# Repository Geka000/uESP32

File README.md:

# uESP32

Small development board for ESP-WROOM32

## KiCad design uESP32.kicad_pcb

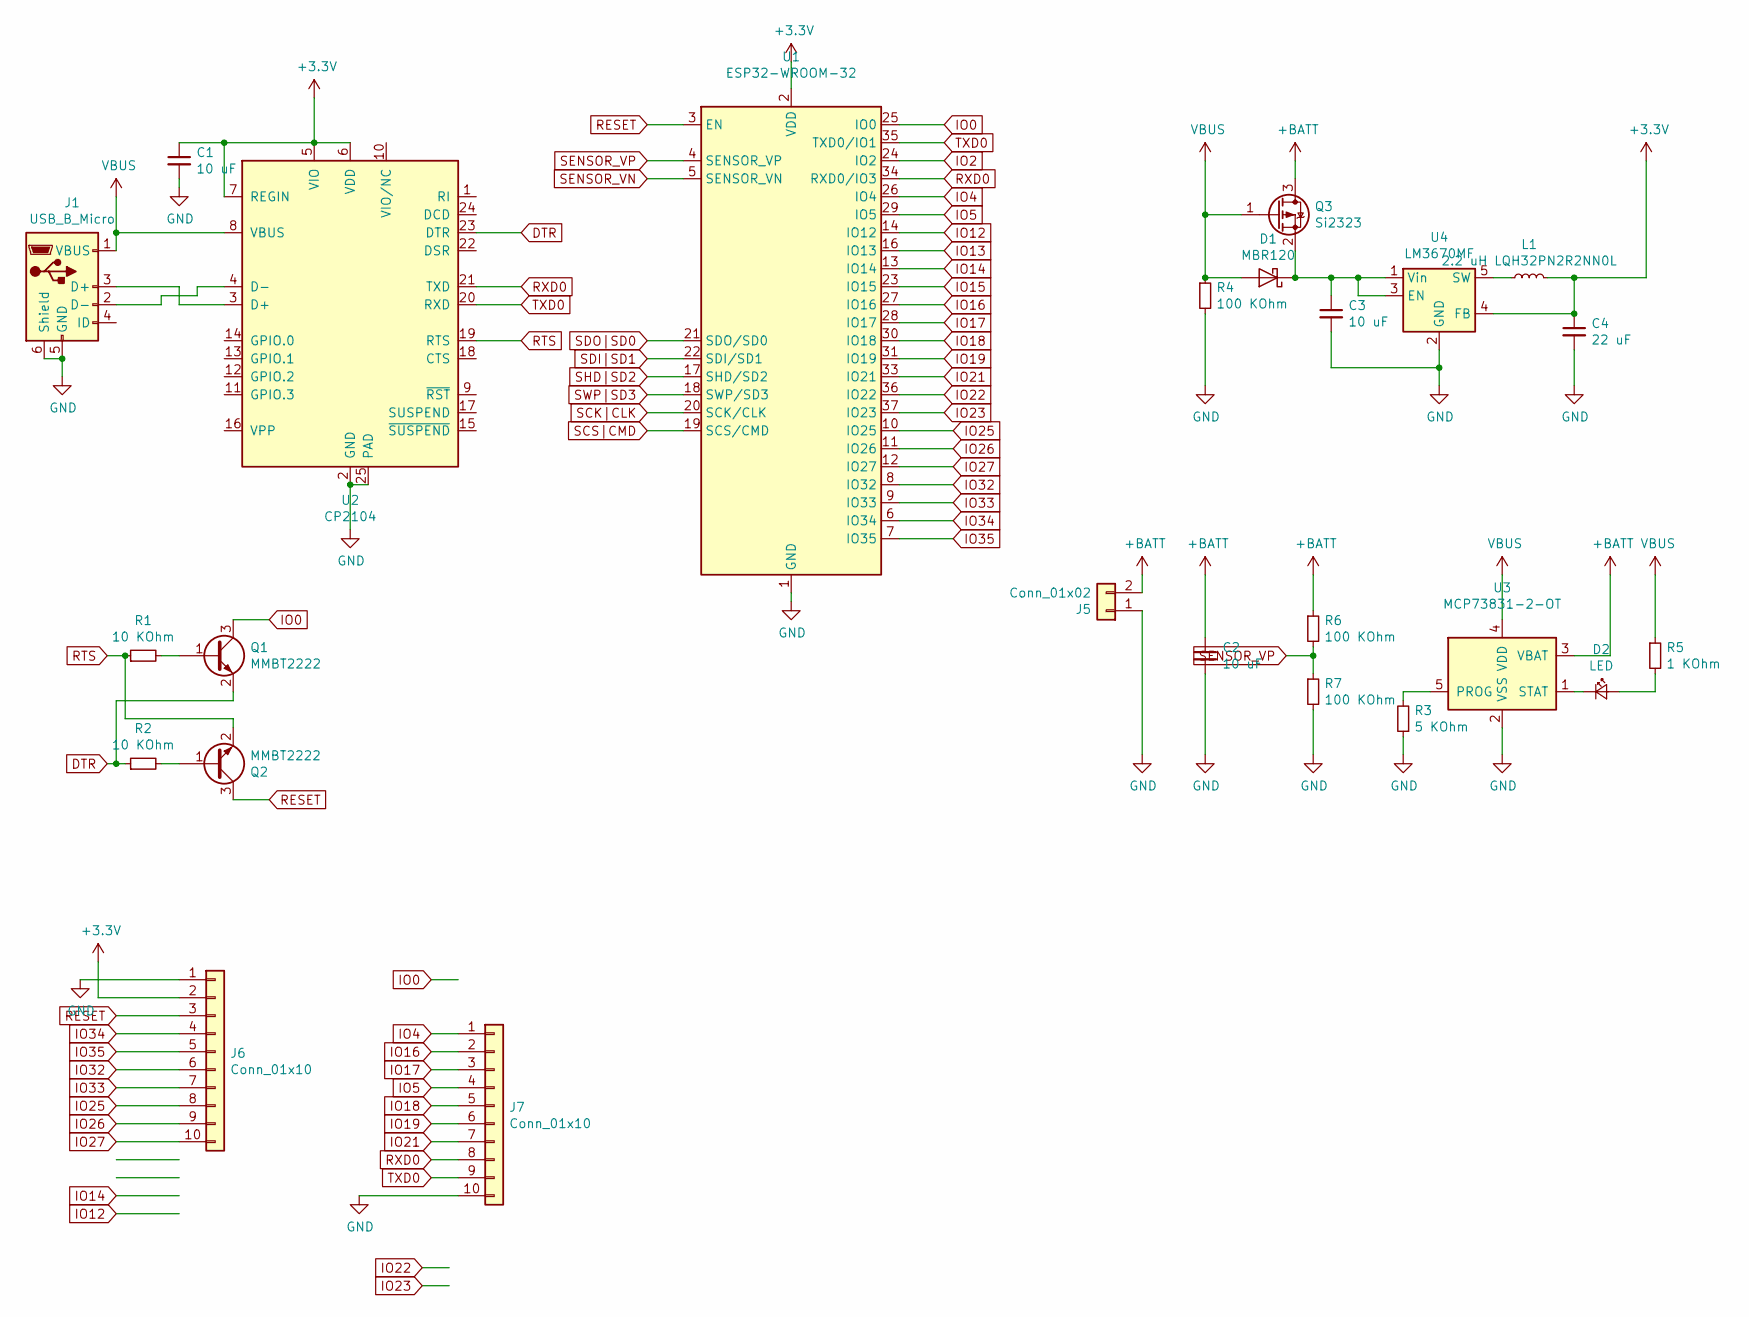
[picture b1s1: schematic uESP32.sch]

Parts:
C1, C2: 10 uF; C_0603_1608Metric
C3: 10 uF; C_0805_2012Metric
C4: 22 uF; C_0805_2012Metric
D1: MBR120; D_SOD-123
D2: LED; LED_1806_4516Metric
J1: USB_B_Micro; USB_Micro-B_Molex_47346-0001
J5: Conn_01x02; JST_GH_BM02B-GHS-TBT_1x02-1MP_P1.25mm_Vertical
J6, J7: Conn_01x10; PinHeader_1x10_P2.54mm_Vertical
L1: 2.2 uH LQH32PN2R2NN0L; L_1210_3225Metric
Q1, Q2: MMBT2222; SOT-23
Q3: Si2323; SOT-23
R1, R2: 10 KOhm; R_0402_1005Metric
R3: 5 KOhm; R_0402_1005Metric
R4, R6, R7: 100 KOhm; R_0402_1005Metric
R5: 1 KOhm; R_0402_1005Metric
U1: ESP32-WROOM-32
U2: CP2104; QFN-24-1EP_4x4mm_P0.5mm_EP2.6x2.6mm
U3: MCP73831-2-OT; SOT-23-5
U4: LM3670MF; TSOT-23-5

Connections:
+3V3: C1.1, C4.1, J6.2, L1.2, U1.2 (VDD), U2.5 (VIO), U2.6 (VDD), U2.7 (REGIN), U4.4 (FB)
+BATT: C2.1, J5.2, Q3.3 (D), R6.1, U3.3 (VBAT)
DTR: Q1.2 (E), R2.1, U2.23 (DTR)
GND: C1.2, C2.2, C3.2, C4.2, J1.5 (GND), J1.6 (Shield), J5.1, J6.1, J7.10, R3.1, R4.2, R7.2, U1.1 (GND), U1.15 (GND), U1.38 (GND), U1.39 (GND), U2.2 (GND), U2.25 (PAD), U3.2 (VSS), U4.2 (GND)
IO0: Q1.3 (C), U1.25 (IO0)
IO2: U1.24 (IO2)
IO4: J7.1, U1.26 (IO4)
IO5: J7.4, U1.29 (IO5)
IO12: U1.14 (IO12)
IO13: U1.16 (IO13)
IO14: U1.13 (IO14)
IO15: U1.23 (IO15)
IO16: J7.2, U1.27 (IO16)
IO17: J7.3, U1.28 (IO17)
IO18: J7.5, U1.30 (IO18)
IO19: J7.6, U1.31 (IO19)
IO21: J7.7, U1.33 (IO21)
IO22: U1.36 (IO22)
IO23: U1.37 (IO23)
IO25: J6.8, U1.10 (IO25)
IO26: J6.9, U1.11 (IO26)
IO27: J6.10, U1.12 (IO27)
IO32: J6.6, U1.8 (IO32)
IO33: J6.7, U1.9 (IO33)
IO34: J6.4, U1.6 (IO34)
IO35: J6.5, U1.7 (IO35)
unnamed: C3.1, D1.1 (K), Q3.2 (S), U4.1 (Vin), U4.3 (EN)
unnamed: D2.1 (K), U3.1 (STAT)
unnamed: D2.2 (A), R5.2
unnamed: J1.2 (D-), U2.4 (D-)
unnamed: J1.3 (D+), U2.3 (D+)
unnamed: L1.1, U4.5 (SW)
unnamed: Q1.1 (B), R1.2
unnamed: Q2.1 (B), R2.2
unnamed: R3.2, U3.5 (PROG)
RESET: J6.3, Q2.3 (C), U1.3 (EN)
RTS: Q2.2 (E), R1.1, U2.19 (RTS)
RXD0: J7.8, U1.34 (RXD0/IO3), U2.21 (TXD)
SCK|CLK: U1.20 (SCK/CLK)
SCS|CMD: U1.19 (SCS/CMD)
SDI|SD1: U1.22 (SDI/SD1)
SDO|SD0: U1.21 (SDO/SD0)
SENSOR_VN: U1.5 (SENSOR_VN)
SENSOR_VP: R6.2, R7.1, U1.4 (SENSOR_VP)
SHD|SD2: U1.17 (SHD/SD2)
SWP|SD3: U1.18 (SWP/SD3)
TXD0: J7.9, U1.35 (TXD0/IO1), U2.20 (RXD)
VBUS: D1.2 (A), J1.1 (VBUS), Q3.1 (G), R4.1, R5.1, U2.8 (VBUS), U3.4 (VDD)

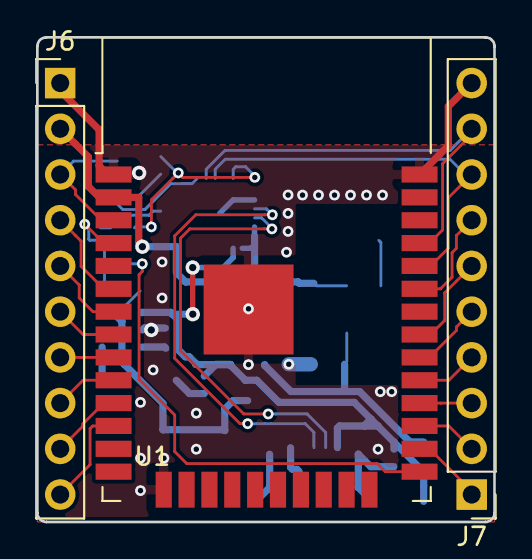
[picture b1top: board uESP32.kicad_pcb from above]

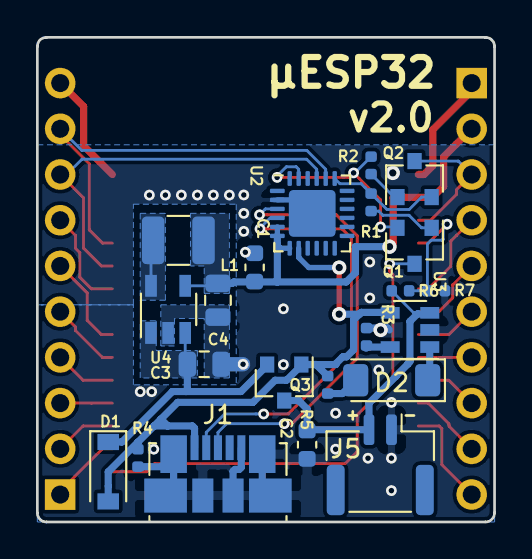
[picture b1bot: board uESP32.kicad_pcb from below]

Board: 2 copper layers, 25.4 x 26.9 mm, 25 parts (22 on the bottom side), 34 nets.

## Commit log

2020-03-15 schematics and pcb
2020-05-11 version 2 2.54 pin header
